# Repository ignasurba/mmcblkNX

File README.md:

# mmcblkNX
Hardware eMMC reader capable of reading *Nintendo Switch* raw partitions including **boot0**, **boot1** with rtsx Linux driver.

# About
eMMC chips wear out, and recovery can be tricky.  
Luckily, the Nintendo Switch (except Lite) has a removable eMMC board.  
It is encrypted, but still readable and writable as raw partitions.  
  
When the eMMC fails it often becomes read-only or worse - corrupt.  
I have recovered a couple broken Nintendo this way, it might help you too!

# How it works
Almost any SD card reader can read eMMC chips. However they only access the main partitions.  
After discovering a Realtek card reader with rtsx Linux driver in an old laptop,  
I could read the boot0 and boot1 partitions too.

# Hardware
It is fully open-source reader based on Realtek **RTS5170** card reader and designed in KiCad.  
Uses the same Molex 500913-0302 connector.

# Software
Requires Linux and rtsx drivers to be installed.  
Works out of the box with Ubuntu 20.04.1  
How to build the required drivers for Raspberry Pi 4 is [here](https://github.com/ignasurba/mmcblkNX/blob/main/raspberry4.md).
  
Read and write speed is about 20MB/s. (USB 2.0)

## Usage
```
sudo dd if=/dev/mmcblk0boot0 of=boot0.bin
sudo dd if=/dev/mmcblk0boot1 of=boot1.bin
sudo dd if=/dev/mmcblk0 of=rawnand.bin
```

## Disable read-only mode
```
sudo su
echo 0 > /sys/block/mmcblk0/force_ro
echo 0 > /sys/block/mmcblk0boot0/force_ro
echo 0 > /sys/block/mmcblk0boot1/force_ro
exit
```

# Where can I get one
I made a small batch and they are available on Tindie.  
https://www.tindie.com/products/22851/  
Or feel free to assemble one yourself.

# Disclaimer
It does not decrypt your files or enable piracy of any kind.  
It is created to make recovery possible.  
In full support of the right to repair movement.

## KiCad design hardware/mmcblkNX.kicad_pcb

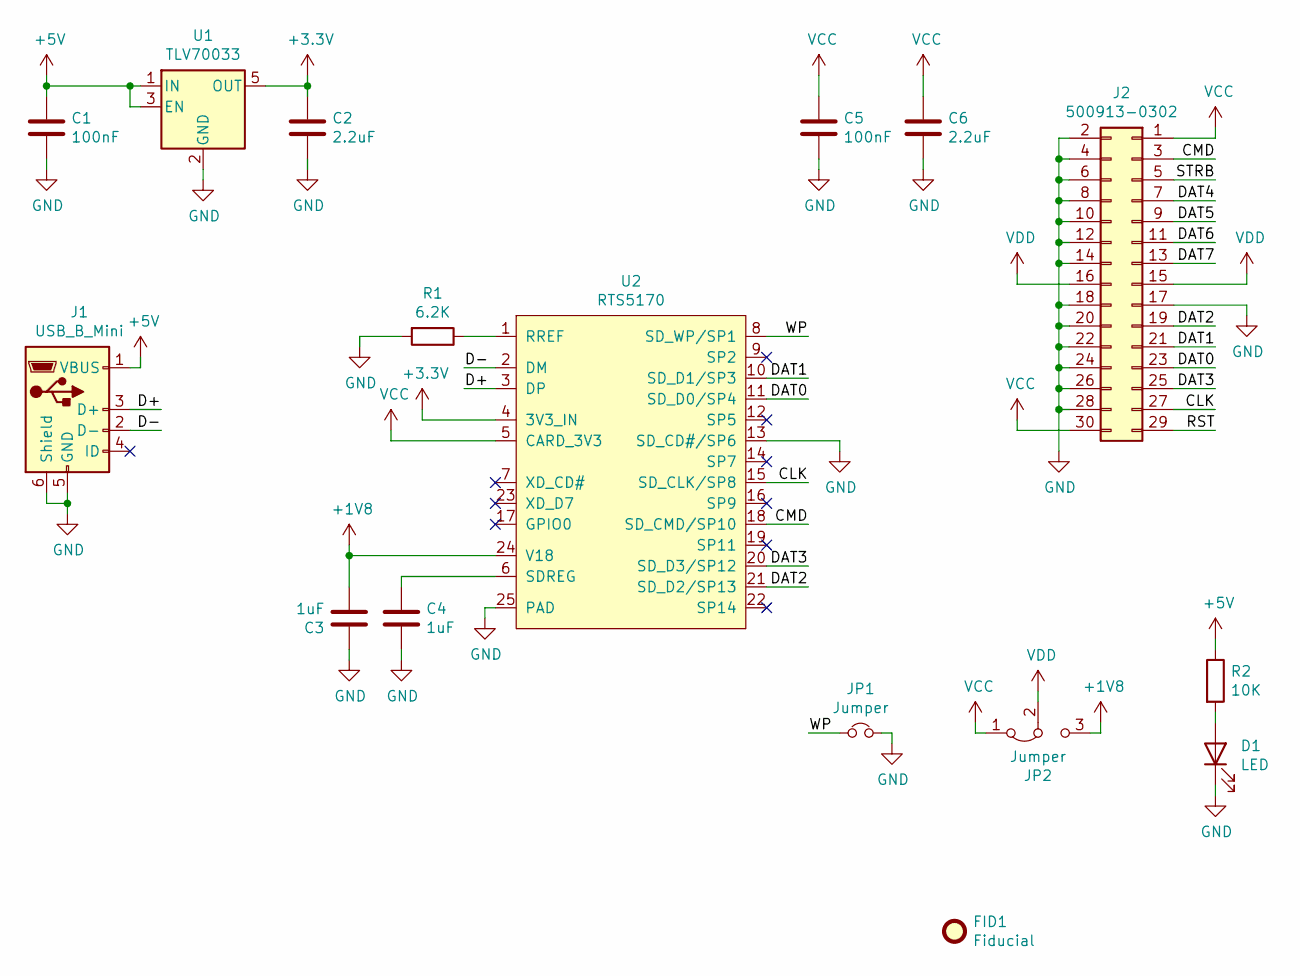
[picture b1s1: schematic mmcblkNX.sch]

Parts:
C1, C5: 100nF; C_0805_2012Metric
C2, C6: 2.2uF; C_0805_2012Metric
C3, C4: 1uF; C_0805_2012Metric
D1: LED; LED_0805_2012Metric
FID1: Fiducial; Fiducial_1mm_Mask2mm
J1: USB_B_Mini; USB_Mini-B_Lumberg_2486_01_Horizontal
J2: 500913-0302
JP1: Jumper; SolderJumper-2_P1.3mm_Bridged_RoundedPad1.0x1.5mm
JP2: Jumper; SolderJumper-3_P1.3mm_Bridged12_RoundedPad1.0x1.5mm
R1: 6.2K; R_0805_2012Metric
R2: 10K; R_0805_2012Metric
U1: TLV70033; SOT-23-5
U2: RTS5170; QFN-24-1EP_4x4mm_P0.5mm_EP2.6x2.6mm

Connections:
+1V8: C3.2, JP2.3 (B), U2.24 (V18)
+3V3: C2.1, U1.5 (OUT), U2.4 (3V3_IN)
+5V: C1.1, J1.1 (VBUS), R2.1, U1.1 (IN), U1.3 (EN)
/CLK: J2.27, U2.15 (SD_CLK/SP8)
/CMD: J2.3, U2.18 (SD_CMD/SP10)
/D+: J1.3 (D+), U2.3 (DP)
/D-: J1.2 (D-), U2.2 (DM)
/DAT0: J2.23, U2.11 (SD_D0/SP4)
/DAT1: J2.21, U2.10 (SD_D1/SP3)
/DAT2: J2.19, U2.21 (SD_D2/SP13)
/DAT3: J2.25, U2.20 (SD_D3/SP12)
/DAT4: J2.7
/DAT5: J2.9
/DAT6: J2.11
/DAT7: J2.13
/RST: J2.29
/STRB: J2.5
/WP: JP1.1, U2.8 (SD_WP/SP1)
GND: C1.2, C2.2, C3.1, C4.2, C5.2, C6.2, D1.1 (K), J1.5 (GND), J1.6 (Shield), J2.2, J2.4, J2.6, J2.8, J2.10, J2.12, J2.14, J2.17, J2.18, J2.20, J2.22, J2.24, J2.26, J2.28, JP1.2, R1.2, U1.2 (GND), U2.13 (SD_CD#/SP6), U2.25 (PAD)
unnamed: C4.1, U2.6 (SDREG)
unnamed: D1.2 (A), R2.2
unnamed: R1.1, U2.1 (RREF)
VCC: C5.1, C6.1, J2.1, J2.30, JP2.1 (A), U2.5 (CARD_3V3)
VDD: J2.15, J2.16, JP2.2 (C)

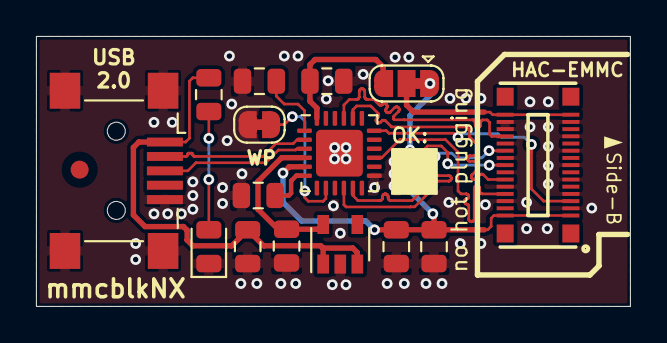
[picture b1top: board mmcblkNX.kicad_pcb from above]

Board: 2 copper layers, 33.0 x 15.0 mm, 16 parts (0 on the bottom side), 18 nets.

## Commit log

2021-02-24 first batch files
2021-02-24 manufacturing test scripts
2021-02-24 update link
2021-12-16 changed method for raspberrypi 5.10.63-v7l+
